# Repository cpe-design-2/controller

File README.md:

# `goco controller`

## Overview

Video game controller source code for the `goco` open-source video game Godot console.

## Details

The controller supports sending key presses using the traditional W/A/S/D button configuration for digital movement and A/B/X/Y button configuration for user action types. There are additionally two more digital buttons for HOME and PAUSE interactions. 

The controller also supports an analog input via joystick that is detected by a computer as a mouse device.

## Building

A makefile is provided to aid in common development commands.

1. Compile the source code:
```
make cc
```

2. Upload the binaries to the plugged-in Arduino Leonardo board:
```
make up
```

## Dependencies

- arduino-cli (see [getting started](https://arduino.github.io/arduino-cli/0.29/getting-started/) for initial setup)
- GNU Make

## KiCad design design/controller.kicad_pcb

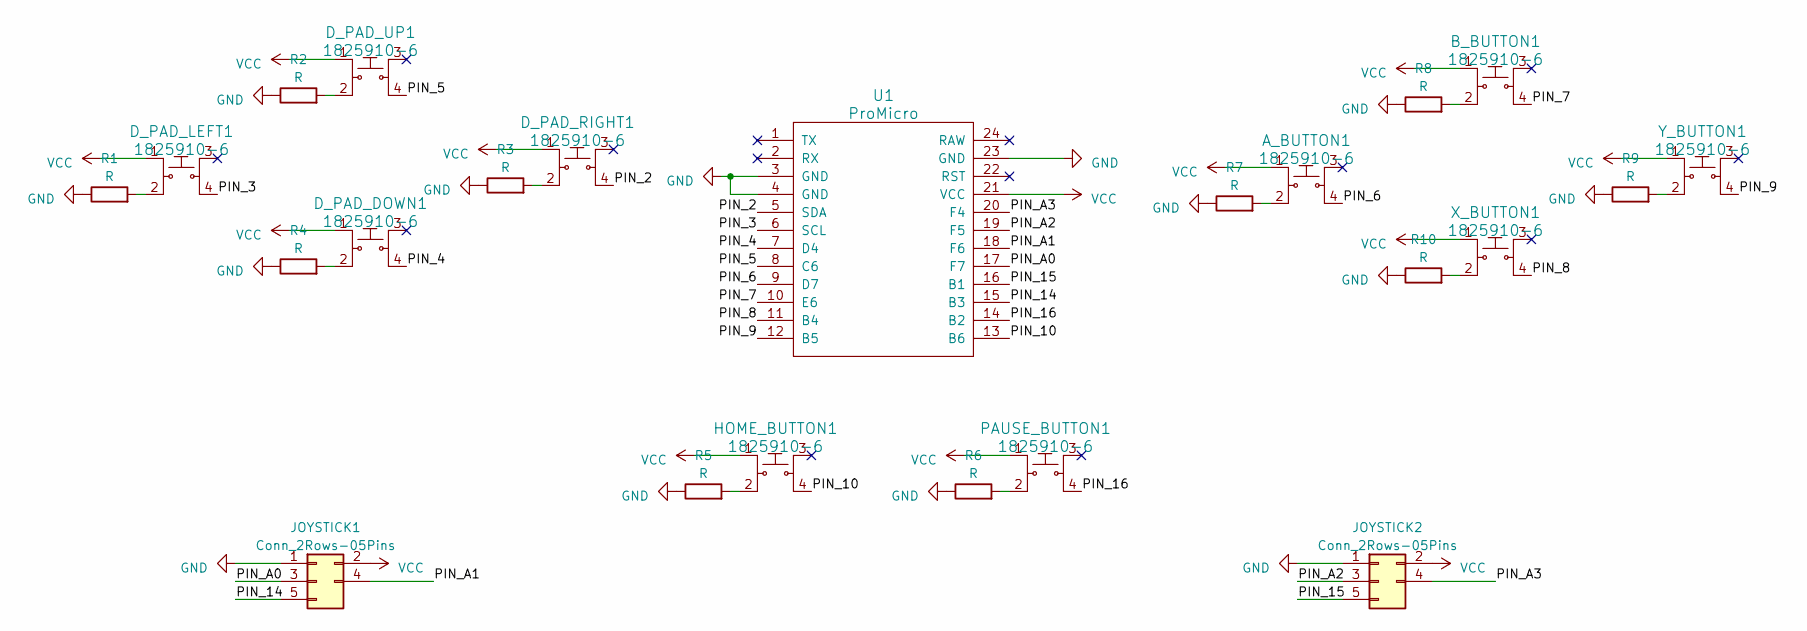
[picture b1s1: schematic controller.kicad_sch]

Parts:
A_BUTTON1: 1825910-6; SW_PUSH_4_PIN; MPN 1825910-6; Digi-Key_PN 450-1650-ND
B_BUTTON1: 1825910-6; SW_PUSH_4_PIN; MPN 1825910-6; Digi-Key_PN 450-1650-ND
D_PAD_DOWN1: 1825910-6; SW_PUSH_4_PIN; MPN 1825910-6; Digi-Key_PN 450-1650-ND
D_PAD_LEFT1: 1825910-6; SW_PUSH_4_PIN; MPN 1825910-6; Digi-Key_PN 450-1650-ND
D_PAD_RIGHT1: 1825910-6; SW_PUSH_4_PIN; MPN 1825910-6; Digi-Key_PN 450-1650-ND
D_PAD_UP1: 1825910-6; SW_PUSH_4_PIN; MPN 1825910-6; Digi-Key_PN 450-1650-ND
HOME_BUTTON1: 1825910-6; SW_PUSH_4_PIN; MPN 1825910-6; Digi-Key_PN 450-1650-ND
JOYSTICK1, JOYSTICK2: Conn_2Rows-05Pins; PinSocket_1x05_P2.54mm_Vertical
PAUSE_BUTTON1: 1825910-6; SW_PUSH_4_PIN; MPN 1825910-6; Digi-Key_PN 450-1650-ND
R1, R2, R3, R4, R5, R6, R7, R8, R9, R10: R; R_Axial_DIN0207_L6.3mm_D2.5mm_P10.16mm_Horizontal
U1: ProMicro
X_BUTTON1: 1825910-6; SW_PUSH_4_PIN; MPN 1825910-6; Digi-Key_PN 450-1650-ND
Y_BUTTON1: 1825910-6; SW_PUSH_4_PIN; MPN 1825910-6; Digi-Key_PN 450-1650-ND

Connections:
/PIN_2: D_PAD_RIGHT1.4, U1.5 (SDA)
/PIN_3: D_PAD_LEFT1.4, U1.6 (SCL)
/PIN_4: D_PAD_DOWN1.4, U1.7 (D4)
/PIN_5: D_PAD_UP1.4, U1.8 (C6)
/PIN_6: A_BUTTON1.4, U1.9 (D7)
/PIN_7: B_BUTTON1.4, U1.10 (E6)
/PIN_8: U1.11 (B4), X_BUTTON1.4
/PIN_9: U1.12 (B5), Y_BUTTON1.4
/PIN_10: HOME_BUTTON1.4, U1.13 (B6)
/PIN_14: JOYSTICK1.5, U1.15 (B3)
/PIN_15: JOYSTICK2.5, U1.16 (B1)
/PIN_16: PAUSE_BUTTON1.4, U1.14 (B2)
/PIN_A0: JOYSTICK1.3, U1.17 (F7)
/PIN_A1: JOYSTICK1.4, U1.18 (F6)
/PIN_A2: JOYSTICK2.3, U1.19 (F5)
/PIN_A3: JOYSTICK2.4, U1.20 (F4)
GND: JOYSTICK1.1, JOYSTICK2.1, R1.1, R2.1, R3.1, R4.1, R5.1, R6.1, R7.1, R8.1, R9.1, R10.1, U1.3 (GND), U1.4 (GND), U1.23 (GND)
unnamed: A_BUTTON1.2, R7.2
unnamed: B_BUTTON1.2, R8.2
unnamed: D_PAD_DOWN1.2, R4.2
unnamed: D_PAD_LEFT1.2, R1.2
unnamed: D_PAD_RIGHT1.2, R3.2
unnamed: D_PAD_UP1.2, R2.2
unnamed: HOME_BUTTON1.2, R5.2
unnamed: PAUSE_BUTTON1.2, R6.2
unnamed: R9.2, Y_BUTTON1.2
unnamed: R10.2, X_BUTTON1.2
VCC: A_BUTTON1.1, B_BUTTON1.1, D_PAD_DOWN1.1, D_PAD_LEFT1.1, D_PAD_RIGHT1.1, D_PAD_UP1.1, HOME_BUTTON1.1, JOYSTICK1.2, JOYSTICK2.2, PAUSE_BUTTON1.1, U1.21 (VCC), X_BUTTON1.1, Y_BUTTON1.1

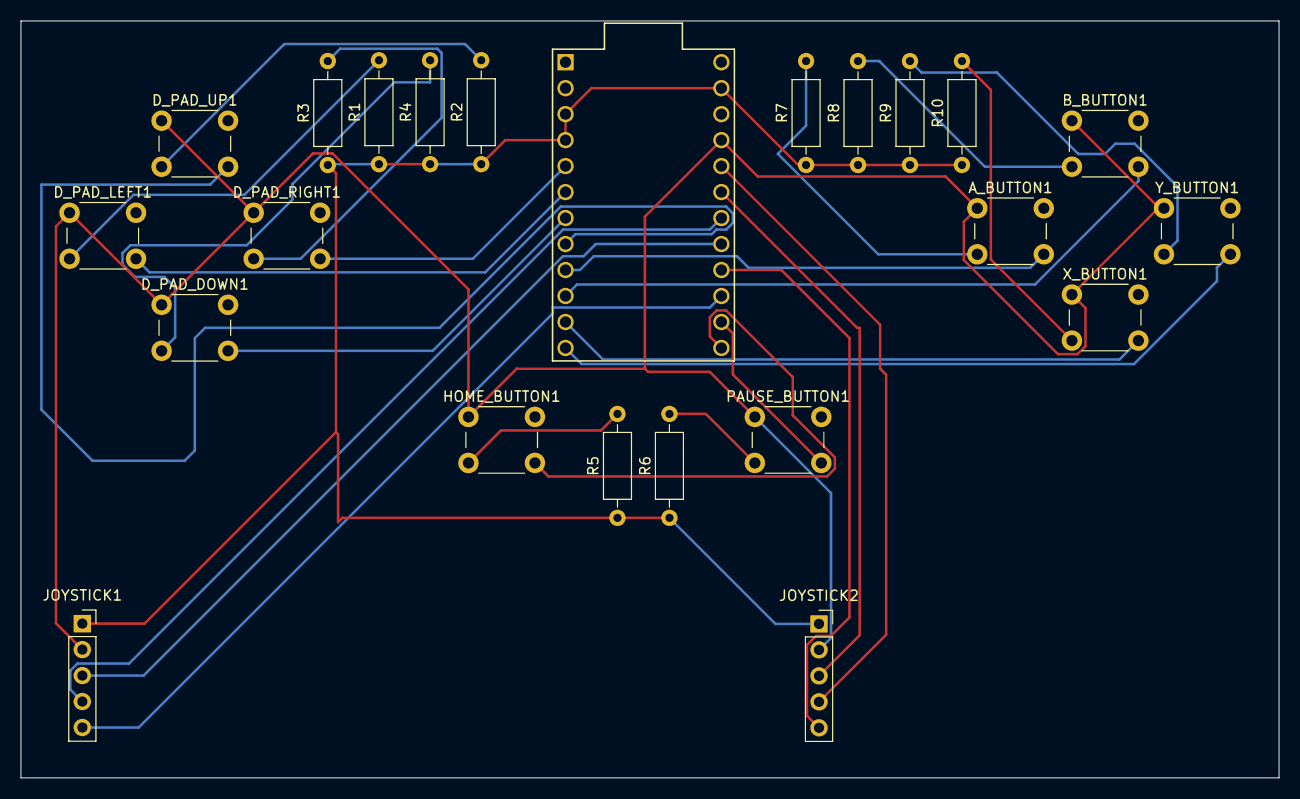
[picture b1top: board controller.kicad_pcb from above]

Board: 2 copper layers, 123.0 x 74.0 mm, 23 parts (0 on the bottom side), 28 nets.

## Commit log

2023-01-15 adds supportive building files and beginning code
2023-01-15 updates readme
2023-01-26 Basic key presses for controller
2023-01-27 Controller Schematics
2023-01-27 ControllerDesign
2023-01-27 moves schematics to docs/ folder
2023-02-11 Mouse Movement
    - Adding in Mouse Movement
    - Fixing WASD Control
    - Adding delay for de-bouncing
2023-02-17 updates readme and adds license
2023-03-09 Adding in Kicad files
2023-03-21 Fixing controller design documents
2023-03-29 Updating Desgin Files
    Adding in Gerber files, removing unnecessary files
2023-03-30 More Design File Changes
2023-03-30 Adding library
2023-04-11 Controller
2023-04-11 updates main to support keyboard or gamepad layout
2023-04-11 Adding in keyboard support again
2023-04-11 fixes mouse movement and speed

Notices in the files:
README.md:
License: MIT
